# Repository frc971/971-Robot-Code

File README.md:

# **THIS REPO IS NOW ARCHIVED AND READ ONLY.**

# Introduction
This is FRC Team 971's main code repository. There are `README*` files throughout the source tree documenting specifics for their respective folders.

## Contributing
Submissions must be made under the terms of the following Developer Certificate of Origin.

By making a contribution to this project, I certify that:

        (a) The contribution was created in whole or in part by me and I
            have the right to submit it under the open source license
            indicated in the file; or

        (b) The contribution is based upon previous work that, to the best
            of my knowledge, is covered under an appropriate open source
            license and I have the right under that license to submit that
            work with modifications, whether created in whole or in part
            by me, under the same open source license (unless I am
            permitted to submit under a different license), as indicated
            in the file; or

        (c) The contribution was provided directly to me by some other
            person who certified (a), (b) or (c) and I have not modified
            it.

        (d) I understand and agree that this project and the contribution
            are public and that a record of the contribution (including all
            personal information I submit with it, including my sign-off) is
            maintained indefinitely and may be redistributed consistent with
            this project or the open source license(s) involved.

To do this, add the following to your commit message.  Gerrit will enforce that all commits have been signed off.

	Signed-off-by: Random J Developer <random@developer.example.org>

Git has support for adding Signed-off-by lines by using `git commit -s`, or you can setup a git commit hook to automatically sign off your commits.  [Stack Overflow](https://stackoverflow.com/questions/15015894/git-add-signed-off-by-line-using-format-signoff-not-working) has instructions for how to do this if you are interested.

## Table of contents
* [Pathway for new members](#pathway-for-new-members)
    * [Learning C++](#1-learning-c)
        * [XRP](#11-xrp)
    * [Gaining code access](#2-gaining-code-access)
    * [The codelab](#3-the-codelab)
* [Code Reviews](#code-reviews)
    * [Creating SSH Aliases](#creating-ssh-aliases)
* [Codelab](#codelab)
* [Other Information](#other-information)
    * [Roborio Kernel Traces](#roborio-kernel-traces)
    * [Notes on troubleshooting network setup](#notes-on-troubleshooting-network-setup)
    * [LSP Setup for Rust](#lsp-setup-for-rust)
    * [Other resources](#other-resources)

## Pathway for new members

### 1. Learning C++

C++ is what we use to program a majority of the code which runs on the robot.
We generally recommend [this course by codeacademy](https://www.codecademy.com/learn/learn-c-plus-plus) which goes over the basics of C++ as well as OOP.

#### 1.1 XRP

If you are unsure what to work on yet you can start on the [XRP Platform](https://docs.wpilib.org/en/stable/docs/xrp-robot/index.html).
Which basically lets you use smaller robots to learn about robotics through WPILib.

### 2. Gaining code access

You can follow [these steps](./documentation/tutorials/getting-started.md) to access the code.

There is also a document which goes over the basics of using both gerrit and git [here](./documentation/tutorials/git-and-gerrit-basics.md)

### 3. The codelab

Once you have an understanding of C++ and have gone through using all the steps needed to access the code you can start on the codelab, which is a directory living in `frc971/codelab/`. Which goes over a lot of the important introductory information that you need to know to get started when programming the robot.
You can read the [README](./frc971/codelab/README.md), which gives you introduces you to the codelab as well as the concepts you need to understand first.

## Code reviews
We want all code to at least have a second person look it over before it gets merged into the `main` branch. Gerrit has [extensive documentation on starting reviews](https://gerrit-review.googlesource.com/Documentation/user-upload.html).  There is also a good [intro User Guide](https://gerrit-review.googlesource.com/Documentation/intro-user.html) and an [intro to working with Gerrit](https://gerrit-review.googlesource.com/Documentation/intro-gerrit-walkthrough.html) and [Gerrit workflows](https://docs.google.com/presentation/d/1C73UgQdzZDw0gzpaEqIC6SPujZJhqamyqO1XOHjH-uk)

TL;DR: Make and commit your changes, do `git push origin HEAD:refs/for/main`, and then click on the provided link to add reviewers.  If you just upload a change without adding any reviewers, it might sit around for a long time before anybody else notices it.

[git-review](http://manpages.debian.org/cgi-bin/man.cgi?query=git-review) can make the upload process simpler.

To download a commit you can press d or click download on gerrit, then select fetch and paste the command in your terminal. Once you've done that you should switch to a new branch in order to make working on multiple commits easier.
You can do this by doing `git switch -c branch_name`, the branch name can be anything, and will only be public for you, so organize in whatever way you find easy to model.

When programming in C++ we follow [Google's C++ Style Guide](https://google.github.io/styleguide/cppguide.html)

Furthermore, you can run `bazel run //tools/lint:run-ci` to fix linter errors which appear on buildkite.

### Some other useful packages
These aren't strictly necessary to build the code, but Michael found the
additional tools provided by these packages useful to install when working with
the code on May 13, 2018.

> **Note**: These are for local install, most of these tools will be available on the build server

```bash
apt install git
apt install yapf3
apt install python3
apt install bazel
apt install clang-format
```

### Creating ssh aliases

It is also handy to alias logins to the raspberry pi's by adding lines like this to your ~/.ssh/config file:
```console
Host pi-7971-2
    User pi
    ForwardAgent yes
    HostName 10.79.71.102
    StrictHostKeyChecking no
```
or, for the roborio:
```
Host roborio-971
    User admin
    HostName 10.9.71.2
    StrictHostKeyChecking no
```
This allows you to use the alias to `ping`, `ssh`, or run commands like:
```
# Download code to robot #7971's raspberry pi #2
bazel run --config=armv7 -c opt //y2020:download_stripped -- pi-7971-2
```

## Other Information

### Roborio Kernel Traces

Currently (as of 2020.02.26), top tends to produce misleading statistics. As
such, you can get more useful information about CPU usage by using kernel
traces. Sample usage:
```console
# Note that you will need to install the trace-cmd package on the roborio.
# This may be not be a trivial task.
# Start the trace
trace-cmd start -e sched_switch -e workqueue
# Stop the trace
trace-cmd stop
# Save the trace to trace.dat
trace-cmd extract
```
You can then scp the `trace.dat` file to your computer and run `kernelshark
trace.dat` (may require installing the `kernelshark` apt package).

### LSP Setup for Rust

You can run `bazel run //tools:gen_rust_project` to generate a rust-project.json
file which rust-analyzer will pick up. You will need to execute this rule
periodically as it will be outdated whenever the BUILD files change.

> **Note** that there's currently no way to tell rust-analyzer *how* to compile
the code, so while it will give you completion support, go to definition, and
other niceties, it won't show compilation errors or warnings at this point.

### Other resources
  1. Intro to [AOS](./aos/README.md), our robot Operating System
  2. Introductory example: [ping/pong](./aos/events/README.md)
  3. Example of [logging](./aos/events/README.md)

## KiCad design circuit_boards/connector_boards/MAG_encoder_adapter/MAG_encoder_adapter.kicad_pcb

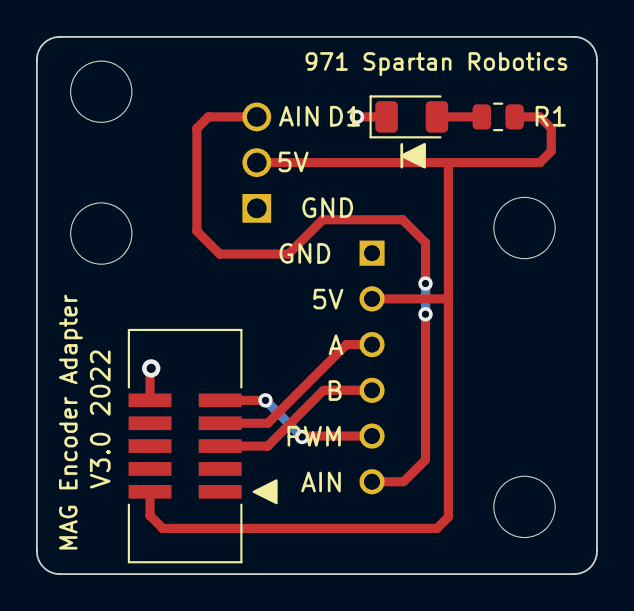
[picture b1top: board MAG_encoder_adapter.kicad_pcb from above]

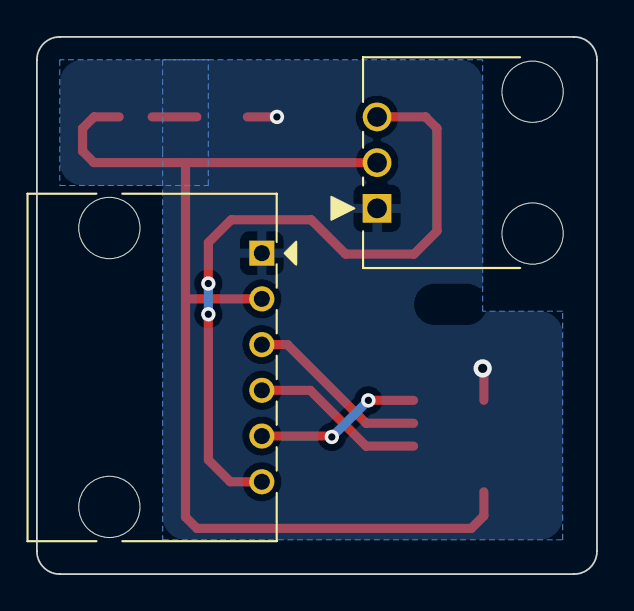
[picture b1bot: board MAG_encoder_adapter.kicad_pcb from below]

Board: 2 copper layers, 31.1 x 29.8 mm, 5 parts (2 on the bottom side), 7 nets.

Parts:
D1: LED; LED_1206_3216Metric
J2: POT; 70555-0002
J3: RIO; 705550005
R1: 2.0k 1%; R_0805_2012Metric
locked: Mag-encoder; 20021521-00010T1LF

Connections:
+5V: J2.2, J3.2, R1.2, locked.2
/A: J3.3, locked.7
/AIN: J2.3, J3.6
/B: J3.4, locked.5
/PWM: J3.5, locked.9
GND: D1.1 (K), J2.1, J3.1, locked.10
unnamed: D1.2 (A), R1.1

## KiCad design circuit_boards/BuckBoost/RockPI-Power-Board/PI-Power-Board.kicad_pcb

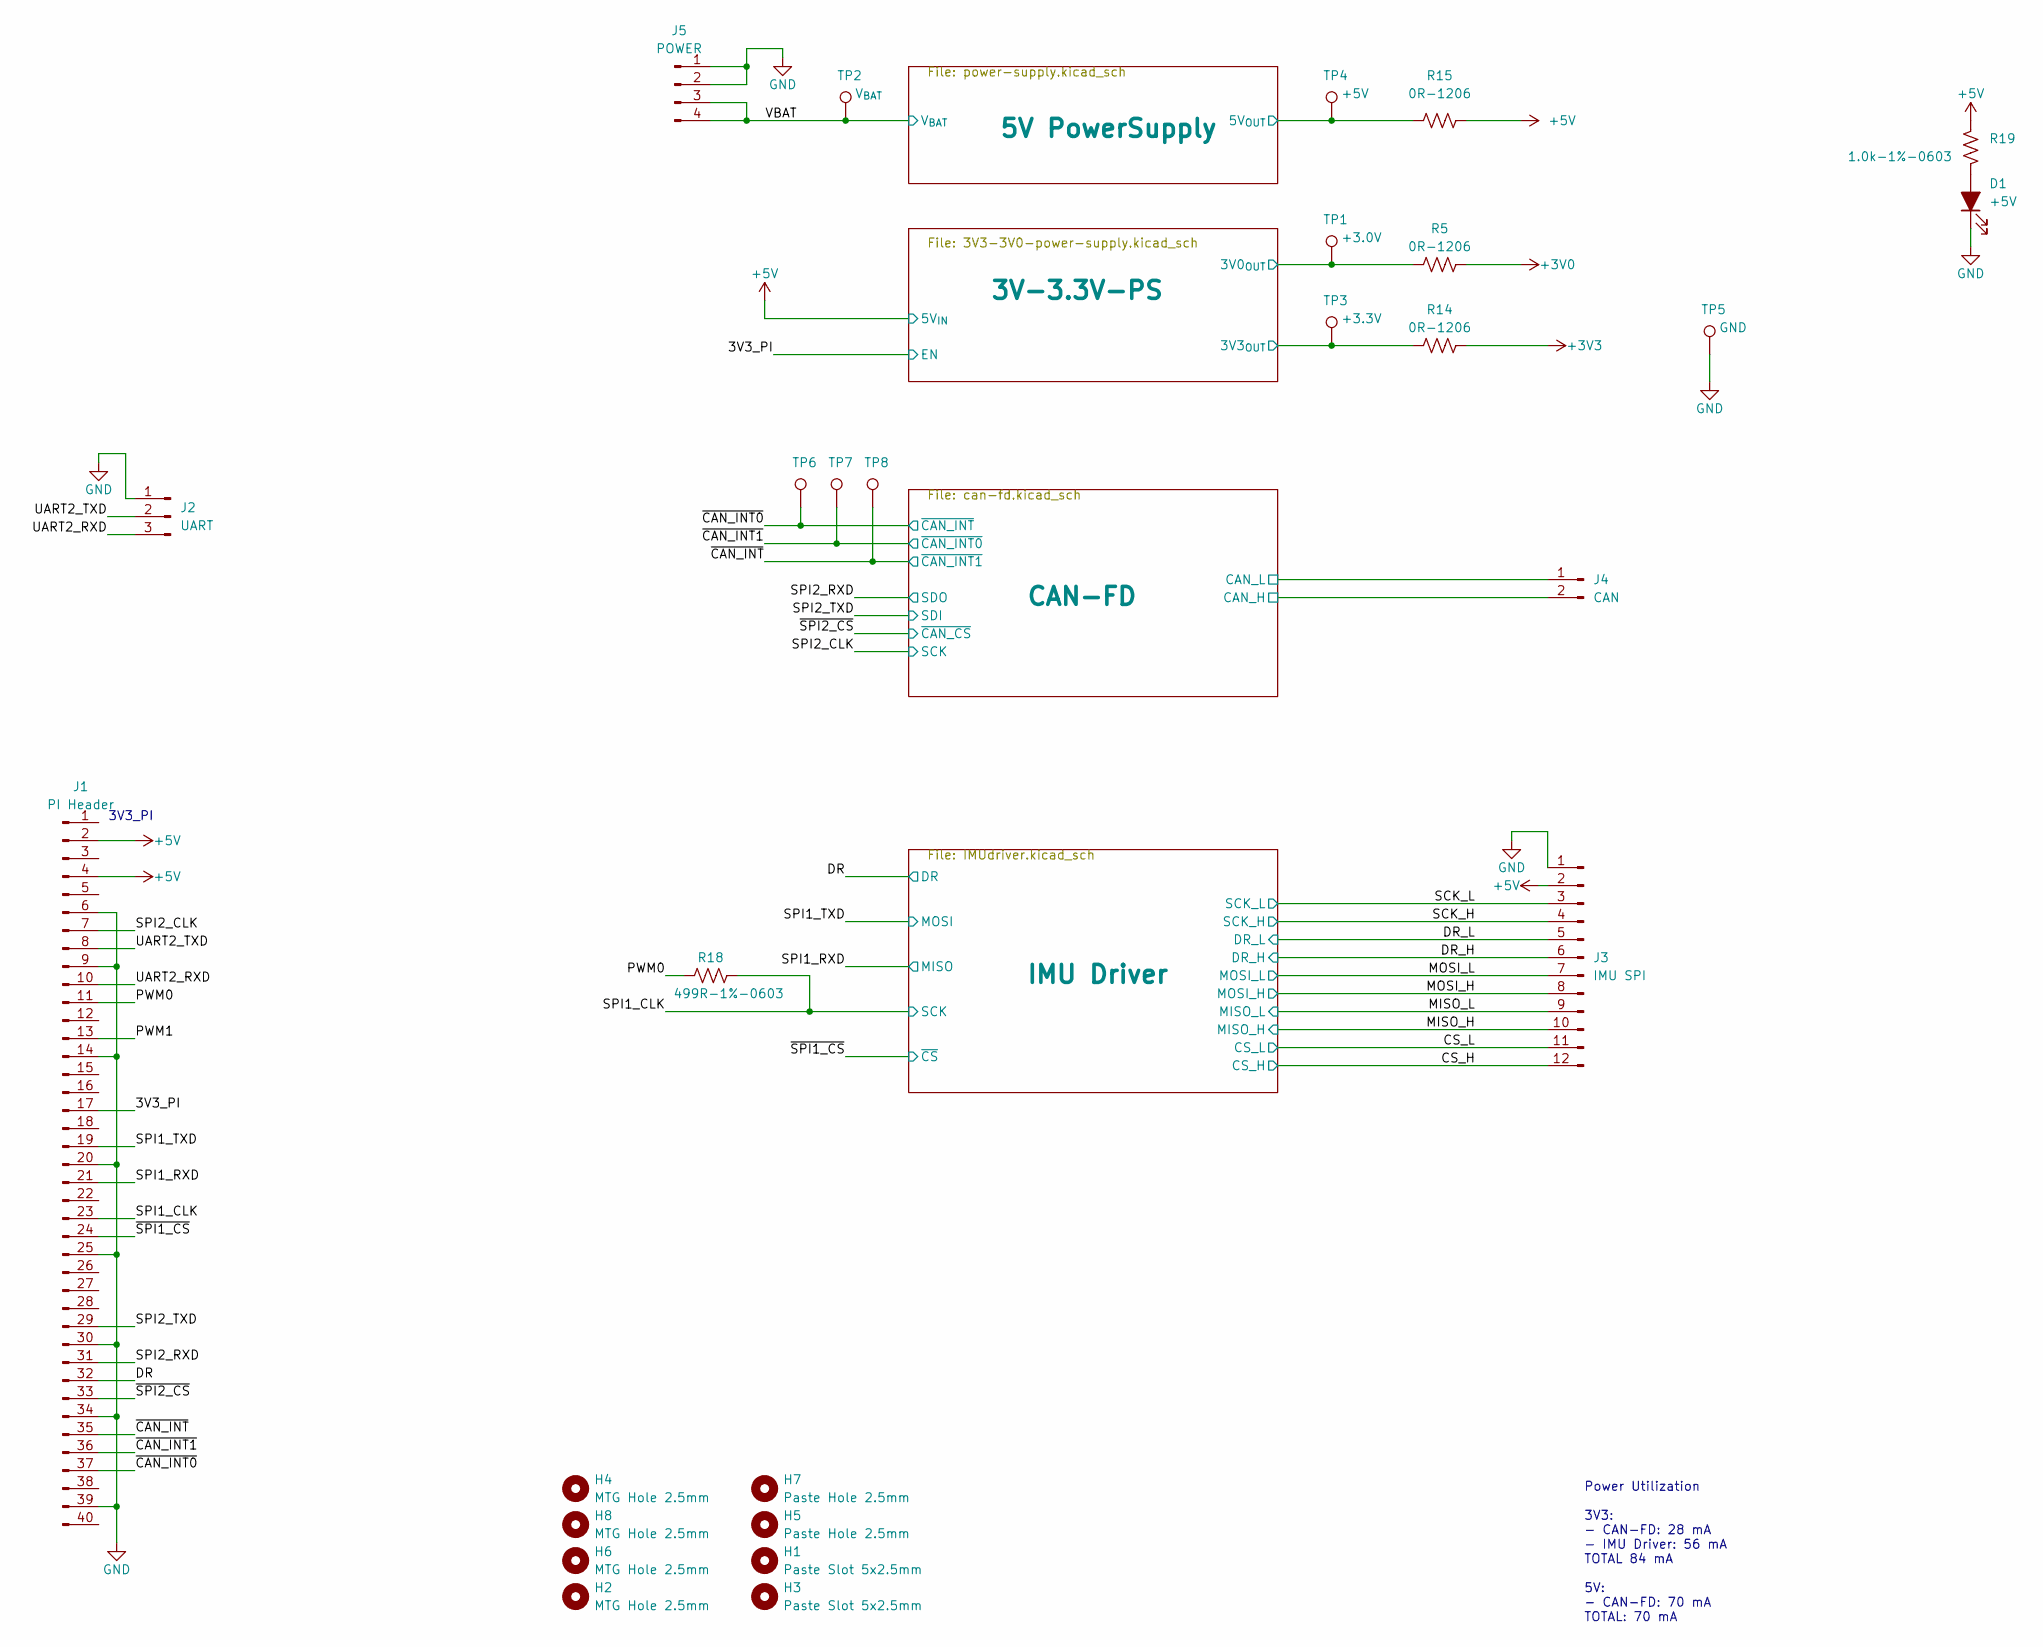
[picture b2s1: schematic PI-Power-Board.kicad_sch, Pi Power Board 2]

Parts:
D1: +5V; LED_1206_3216Metric; MFG P/N QTLP650D4TR
H1, H3: Paste Slot 5x2.5mm; PASTE-SLOT-5x2.5mm
H2, H4, H6, H8: MTG Hole 2.5mm; MountingHole_2.5mm
H5, H7: Paste Hole 2.5mm; PASTE-HOLE-2.5mm
J1: PI Header; M20-782045; MFG P/N M20-7812045
J2: UART; 70555-0002; MFG P/N 70555-0002
J3: IMU SPI; 70555-0011; MFG P/N 70555-0011
J4: CAN; 70555-0001; MFG P/N 70555-0001
J5: POWER; 70555-0003; MFG P/N 70555-0003
R5, R14, R15: 0R-1206; R_1206_3216Metric; MFG P/N RC1206JR-070RL
R18: 499R-1%-0603; R_0603_1608Metric; MFG P/N RC0603FR-07499RL
R19: 1.0k-1%-0603; R_0603_1608Metric; MFG P/N RC0603FR-071KL
TP1: +3.0V; TestPoint_Keystone_5000-5004_Miniature; MFG P/N 5002
TP2: V_{BAT}; TestPoint_Keystone_5000-5004_Miniature; MFG P/N 5002
TP3, TP6, TP7, TP8: +3.3V; TestPoint_Keystone_5000-5004_Miniature; MFG P/N 5002
TP4: +5V; TestPoint_Keystone_5000-5004_Miniature; MFG P/N 5002
TP5: GND; TestPoint_Keystone_5000-5004_Miniature; MFG P/N 5002

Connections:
+3V0: R5.2; also elsewhere on the board
+3V3: R14.2; also elsewhere on the board
+5V: J1.2, J1.4, J3.2, R15.2, R19.2; also elsewhere on the board
/3V3_PI: J1.17; also elsewhere on the board
/3V-3.3V-PS/3V0_{OUT}: R5.1, TP1.1; also elsewhere on the board
/3V-3.3V-PS/3V3_{OUT}: R14.1, TP3.1; also elsewhere on the board
/5V PowerSupply/V_{OSNS}: R15.1, TP4.1; also elsewhere on the board
/CAN-FD/CAN_H: J4.2; also elsewhere on the board
/CAN-FD/CAN_L: J4.1; also elsewhere on the board
/CS_H: J3.12; also elsewhere on the board
/CS_L: J3.11; also elsewhere on the board
/DR: J1.32; also elsewhere on the board
/DR_H: J3.6; also elsewhere on the board
/DR_L: J3.5; also elsewhere on the board
/MISO_H: J3.10; also elsewhere on the board
/MISO_L: J3.9; also elsewhere on the board
/MOSI_H: J3.8; also elsewhere on the board
/MOSI_L: J3.7; also elsewhere on the board
/PWM0: J1.11, R18.1
/PWM1: J1.13
/SCK_H: J3.4; also elsewhere on the board
/SCK_L: J3.3; also elsewhere on the board
/SPI1_CLK: J1.23, R18.2; also elsewhere on the board
/SPI1_RXD: J1.21; also elsewhere on the board
/SPI1_TXD: J1.19; also elsewhere on the board
/SPI2_CLK: J1.7; also elsewhere on the board
/SPI2_RXD: J1.31; also elsewhere on the board
/SPI2_TXD: J1.29; also elsewhere on the board
/UART2_RXD: J1.10, J2.3
/UART2_TXD: J1.8, J2.2
/VBAT: J5.3, J5.4, TP2.1; also elsewhere on the board
/~CAN_INT0: J1.37, TP6.1; also elsewhere on the board
/~CAN_INT1: J1.36, TP7.1; also elsewhere on the board
/~CAN_INT: J1.35, TP8.1; also elsewhere on the board
/~SPI1_CS: J1.24; also elsewhere on the board
/~SPI2_CS: J1.33; also elsewhere on the board
GND: D1.1 (K), J1.6, J1.9, J1.14, J1.20, J1.25, J1.30, J1.34, J1.39, J2.1, J3.1, J5.1, J5.2, TP5.1; also elsewhere on the board
unnamed: D1.2 (A), R19.1

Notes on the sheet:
3V3_PI
Power Utilization 3V3: - CAN-FD: 28 mA - IMU Driver: 56 mA TOTAL 84 mA 5V: - CAN-FD: 70 mA TOTAL: 70 mA

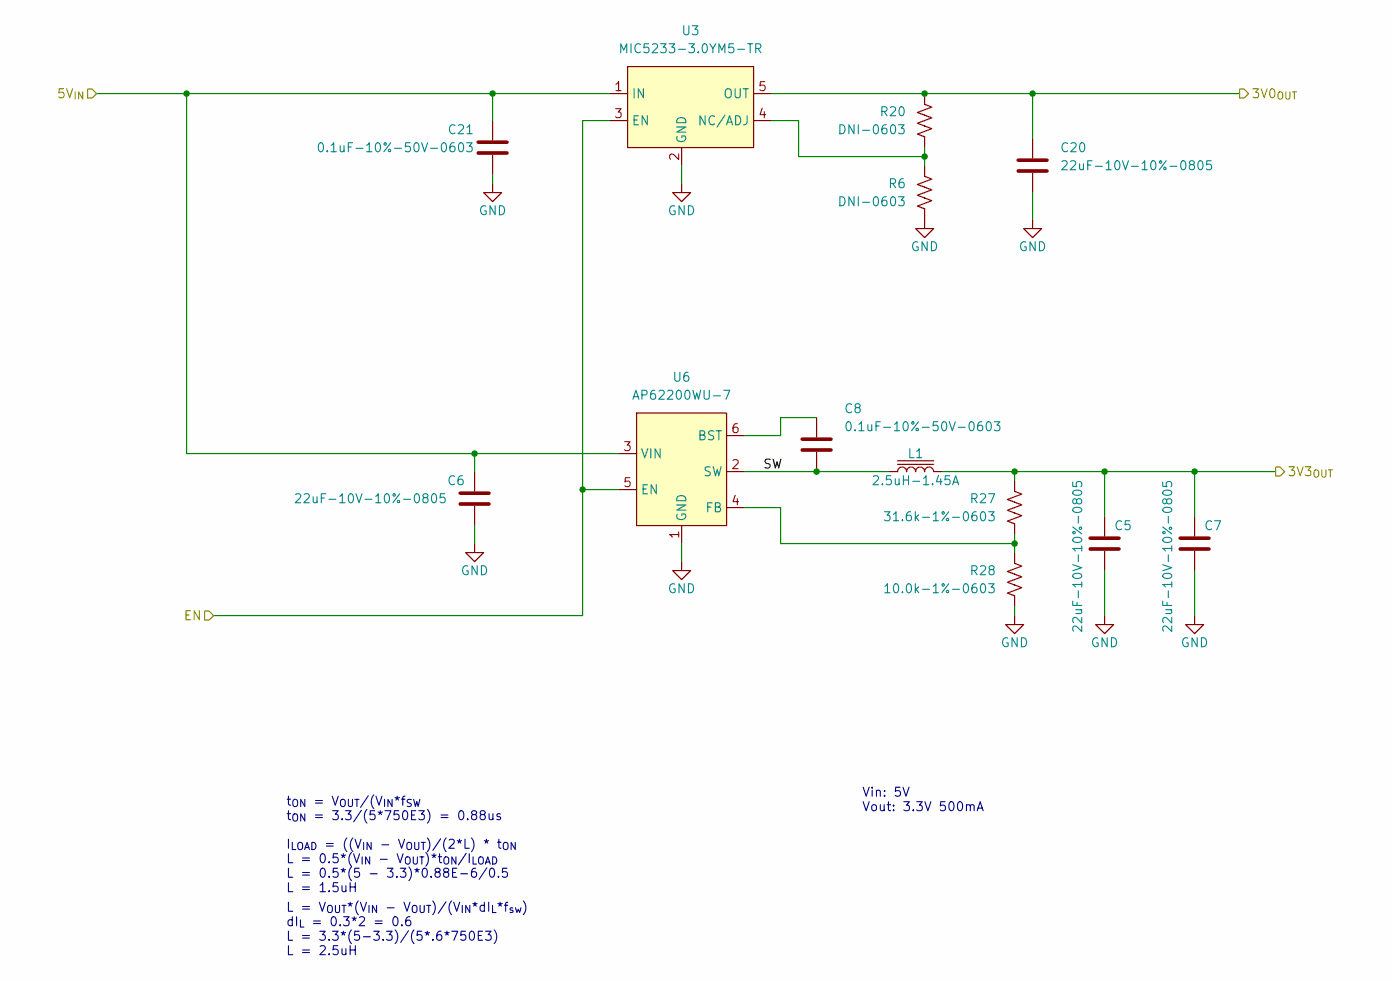
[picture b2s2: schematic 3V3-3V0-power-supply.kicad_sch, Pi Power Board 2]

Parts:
C5, C6, C7, C20: 22uF-10V-10%-0805; C_0805_2012Metric; MFG P/N CL21A226KPCLRNC
C8, C21: 0.1uF-10%-50V-0603; C_0603_1608Metric; MFG P/N CL10B104KB8NNNC
L1: 2.5uH-1.45A; WE-TPC-744031002; MFG P/N 744031002
R6, R20: DNI-0603; R_0603_1608Metric
R27: 31.6k-1%-0603; R_0603_1608Metric; MFG P/N RMCF0603FT31K6
R28: 10.0k-1%-0603; R_0603_1608Metric; MFG P/N RC0603FR-0710KL
U3: MIC5233-3.0YM5-TR; SOT-23-5; MFG P/N MIC5233-3.0YM5-TR
U6: AP62200WU-7; TSOT-23-6; MFG P/N AP62200WU-7

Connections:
+5V: C6.1, C21.1, U3.1 (IN), U6.3 (VIN); also elsewhere on the board
/3V3_PI: U3.3 (EN), U6.5 (EN); also elsewhere on the board
/3V-3.3V-PS/3V0_{OUT}: C20.1, R20.1, U3.5 (OUT); also elsewhere on the board
/3V-3.3V-PS/3V3_{OUT}: C5.1, C7.1, L1.2, R27.1; also elsewhere on the board
/3V-3.3V-PS/SW: C8.2, L1.1, U6.2 (SW)
GND: C5.2, C6.2, C7.2, C20.2, C21.2, R6.2, R28.2, U3.2 (GND), U6.1 (GND); also elsewhere on the board
unnamed: C8.1, U6.6 (BST)
unnamed: R6.1, R20.2, U3.4 (NC/ADJ)
unnamed: R27.2, R28.1, U6.4 (FB)

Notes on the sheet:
Vin: 5V Vout: 3.3V 500mA
I_{LOAD} = ((V_{IN} - V_{OUT})/(2*L) * t_{ON} L = 0.5*(V_{IN} - V_{OUT})*t_{ON}/I_{LOAD} L = 0.5*(5 - 3.3)*0.88E-6/0.5 L = 1.5uH
L = V_{OUT}*(V_{IN} - V_{OUT})/(V_{IN}*dI_{L}*f_{sw}) dI_{L} = 0.3*2 = 0.6 L = 3.3*(5-3.3)/(5*.6*750E3) L = 2.5uH
t_{ON} = V_{OUT}/(V_{IN}*f_{SW} t_{ON} = 3.3/(5*750E3) = 0.88us

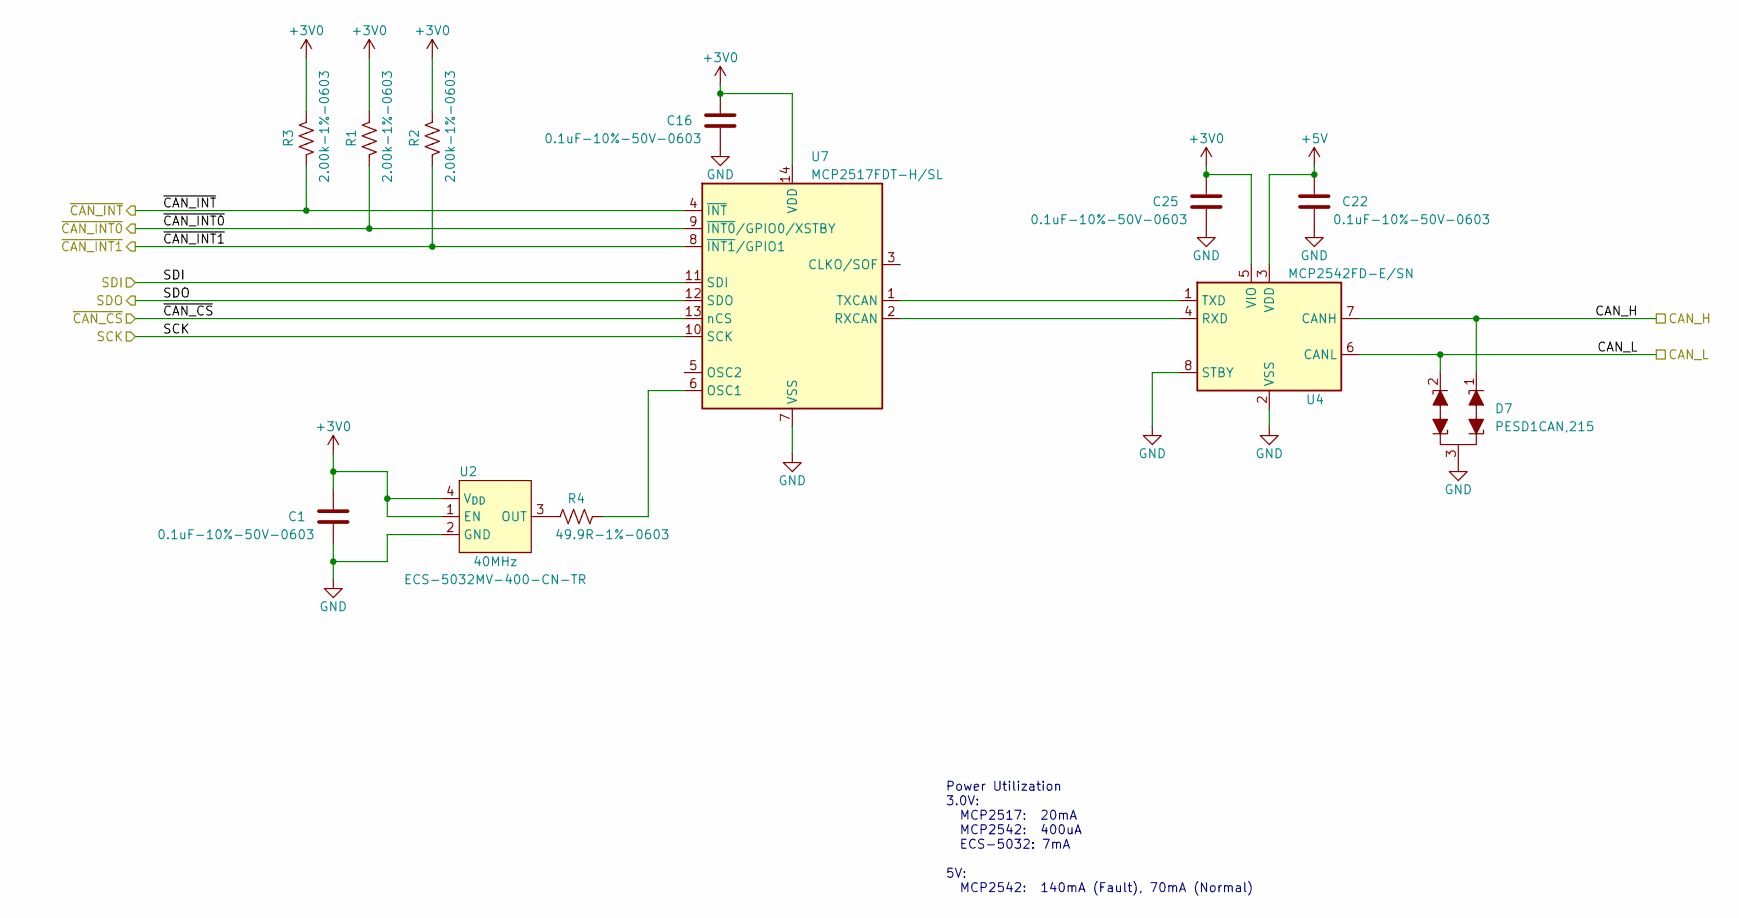
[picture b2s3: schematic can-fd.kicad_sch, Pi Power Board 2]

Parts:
C1, C16, C22, C25: 0.1uF-10%-50V-0603; C_0603_1608Metric; MFG P/N CL10B104KB8NNNC
D7: PESD1CAN; SOT-23; MFG P/N PESD1CAN,215
R1, R2, R3: 2.00k-1%-0603; R_0603_1608Metric; MFG P/N RC0603FR-072KL
R4: 49.9R-1%-0603; R_0603_1608Metric; MFG P/N RC0603FR-0749R9L
U2: 40MHz; ECS-5032MV; MFG P/N ECS-5032MV-400-CN-TR
U4: MCP2542FD-E/SN; SO-8_3.9x4.9mm_P1.27mm; MFG P/N MCP2542FD-E/SN
U7: MCP2517FDT-H/SL; SOIC-14_3.9x8.7mm_P1.27mm; MFG P/N MCP2517FDT-H/SL

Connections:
+3V0: C1.1, C16.1, C25.1, R1.1, R2.1, R3.1, U2.1 (EN), U2.4 (V_{DD}), U4.5 (VIO), U7.14 (VDD); also elsewhere on the board
+5V: C22.1, U4.3 (VDD); also elsewhere on the board
/CAN-FD/CAN_H: D7.1 (K1), U4.7 (CANH); also elsewhere on the board
/CAN-FD/CAN_L: D7.2 (K1), U4.6 (CANL); also elsewhere on the board
/SPI2_CLK: U7.10 (SCK); also elsewhere on the board
/SPI2_RXD: U7.12 (SDO); also elsewhere on the board
/SPI2_TXD: U7.11 (SDI); also elsewhere on the board
/~CAN_INT0: R3.2, U7.4 (~INT); also elsewhere on the board
/~CAN_INT1: R1.2, U7.9 (~INT0/GPIO0/XSTBY); also elsewhere on the board
/~CAN_INT: R2.2, U7.8 (~INT1/GPIO1); also elsewhere on the board
/~SPI2_CS: U7.13 (nCS); also elsewhere on the board
GND: C1.2, C16.2, C22.2, C25.2, D7.3 (KK), U2.2 (GND), U4.2 (VSS), U4.8 (STBY), U7.7 (VSS); also elsewhere on the board
unnamed: R4.1, U2.3 (OUT)
unnamed: R4.2, U7.6 (OSC1)
unnamed: U4.1 (TXD), U7.1 (TXCAN)
unnamed: U4.4 (RXD), U7.2 (RXCAN)

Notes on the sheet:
Power Utilization 3.0V: MCP2517: 20mA MCP2542: 400uA ECS-5032: 7mA 5V: MCP2542: 140mA (Fault), 70mA (Normal)

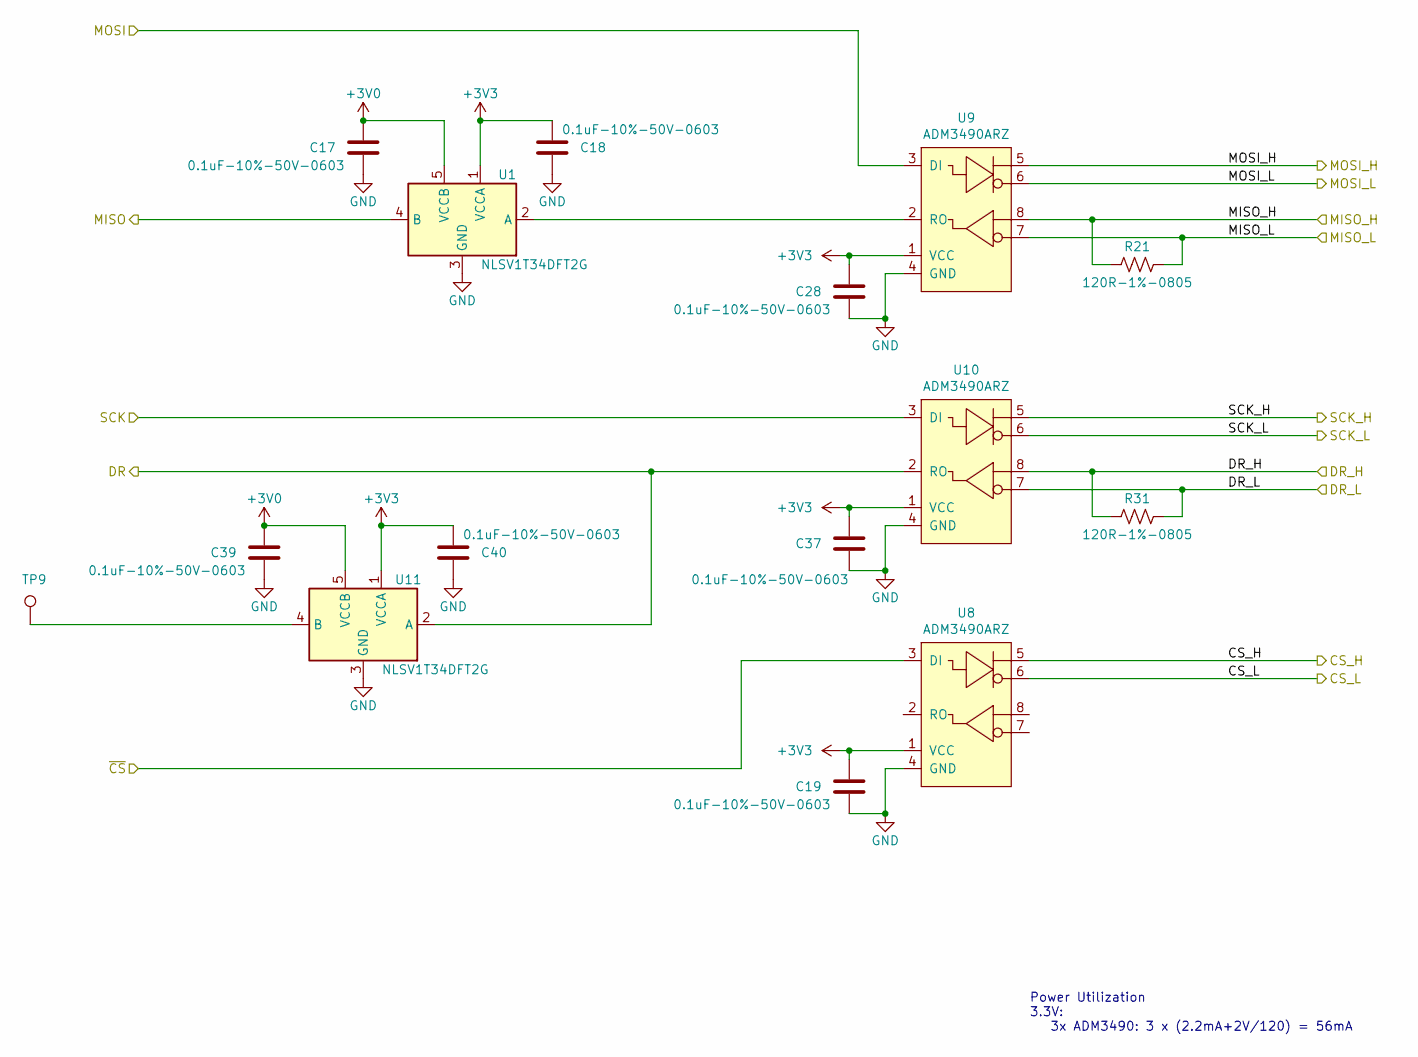
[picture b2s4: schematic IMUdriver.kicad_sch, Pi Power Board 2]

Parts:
C17, C18, C19, C28, C37, C39, C40: 0.1uF-10%-50V-0603; C_0603_1608Metric; MFG P/N CL10B104KB8NNNC
R21, R31: 120R-1%-0805; R_0805_2012Metric; MFG P/N RMCF0805FT120R
TP9: +3.3V; TestPoint_Keystone_5000-5004_Miniature; MFG P/N 5002
U1, U11: NLSV1T34DFT2G; SOT-353_SC-70-5; MFG P/N NLSV1T34DFT2G
U8, U9, U10: ADM3490ARZ; SO-8_3.9x4.9mm_P1.27mm; MFG P/N ADM3490ARZ

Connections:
+3V0: C17.1, C39.1, U1.5 (VCCB), U11.5 (VCCB); also elsewhere on the board
+3V3: C18.1, C19.1, C28.1, C37.1, C40.1, U1.1 (VCCA), U8.1 (VCC), U9.1 (VCC), U10.1 (VCC), U11.1 (VCCA); also elsewhere on the board
/CS_H: U8.5; also elsewhere on the board
/CS_L: U8.6; also elsewhere on the board
/DR: U10.2 (RO), U11.2 (A); also elsewhere on the board
/DR_H: R31.1, U10.8; also elsewhere on the board
/DR_L: R31.2, U10.7; also elsewhere on the board
/MISO_H: R21.1, U9.8; also elsewhere on the board
/MISO_L: R21.2, U9.7; also elsewhere on the board
/MOSI_H: U9.5; also elsewhere on the board
/MOSI_L: U9.6; also elsewhere on the board
/SCK_H: U10.5; also elsewhere on the board
/SCK_L: U10.6; also elsewhere on the board
/SPI1_CLK: U10.3 (DI); also elsewhere on the board
/SPI1_RXD: U1.4 (B); also elsewhere on the board
/SPI1_TXD: U9.3 (DI); also elsewhere on the board
/~SPI1_CS: U8.3 (DI); also elsewhere on the board
GND: C17.2, C18.2, C19.2, C28.2, C37.2, C39.2, C40.2, U1.3 (GND), U8.4 (GND), U9.4 (GND), U10.4 (GND), U11.3 (GND); also elsewhere on the board
unnamed: TP9.1, U11.4 (B)
unnamed: U1.2 (A), U9.2 (RO)

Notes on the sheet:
Power Utilization 3.3V: 3x ADM3490: 3 x (2.2mA+2V/120) = 56mA

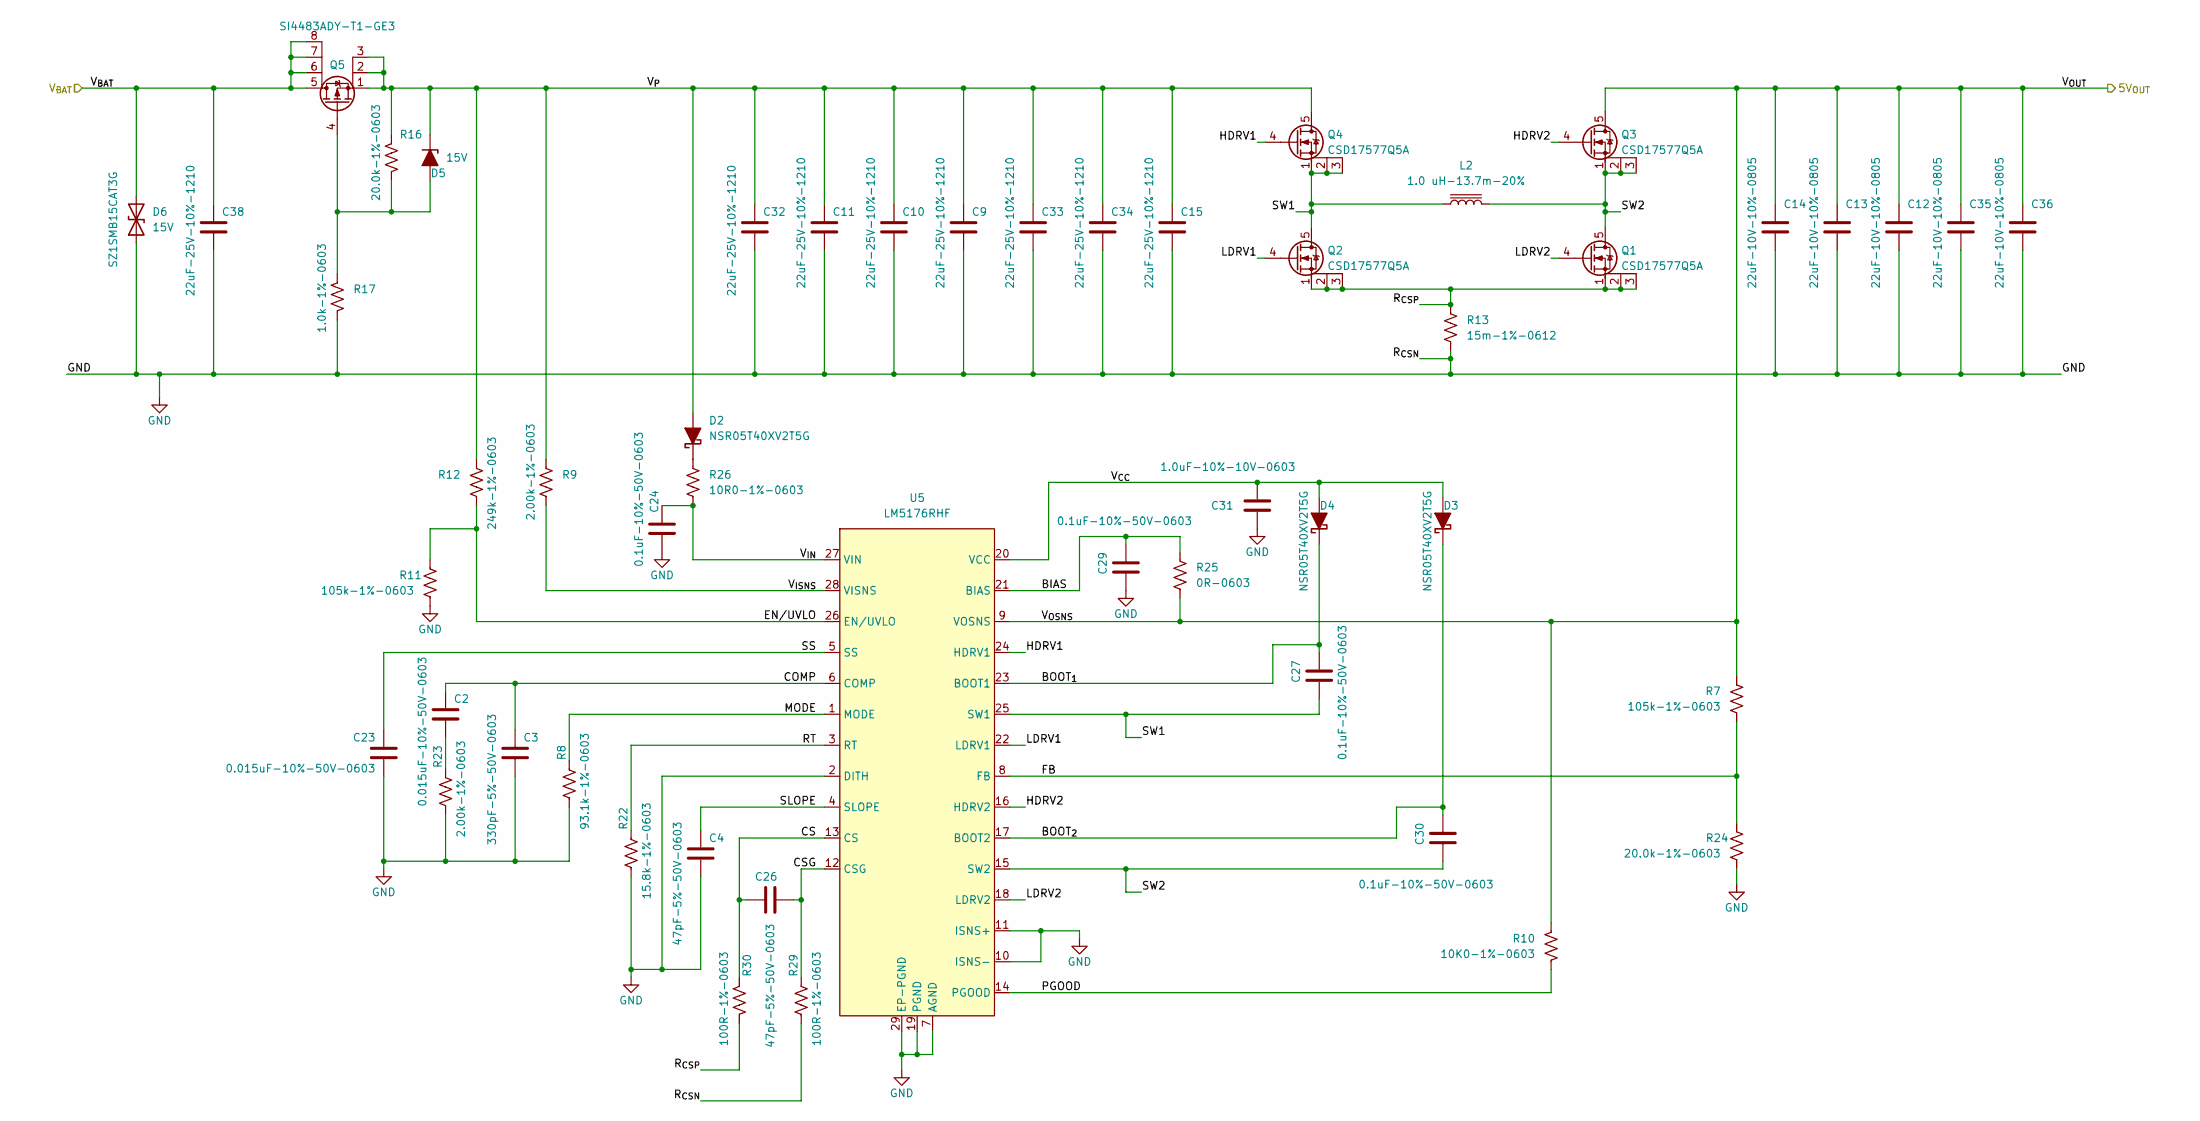
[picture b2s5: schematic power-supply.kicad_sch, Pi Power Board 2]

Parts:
C2, C23: 0.015uF-10%-50V-0603; C_0603_1608Metric; MFG P/N CC0603KRX7R9BB153
C3: 330pF-5%-50V-0603; C_0603_1608Metric; MFG P/N GCM1885C2A331FA16D
C4, C26: 47pF-5%-50V-0603; C_0603_1608Metric; MFG P/N CL10C470JB8NNNC
C9, C10, C11, C15, C32, C33, C34, C38: 22uF-25V-10%-1210; C_1210_3225Metric; MFG P/N GRM32ER61E226KE15L
C12, C13, C14, C35, C36: 22uF-10V-10%-0805; C_0805_2012Metric; MFG P/N CL21A226KPCLRNC
C24, C27, C29, C30: 0.1uF-10%-50V-0603; C_0603_1608Metric; MFG P/N CL10B104KB8NNNC
C31: 1.0uF-10%-10V-0603; C_0603_1608Metric; MFG P/N CL10B105KP8NNNC
D2, D3, D4: NSR05T40XV2T5G; D_SOD-523; MFG P/N NSR05T40XV2T5G
D5: 15V; D_SOD-123F; MFG P/N BZT52H-C15,115
D6: 15V; D_SMB; MFG P/N SZ1SMB15CAT3G
L2: 1.0 uH-13.7m-20%; IHLP2020CZER; MFG P/N IHLP2020CZER1R0M01
Q1, Q2, Q3, Q4: CSD17577Q5A; TI-SON5x6; MFG P/N CSD17577Q5A
Q5: SI4483ADY-T1-GE3; SOIC-8_3.9x4.9mm_P1.27mm; MFG P/N SI4483ADY-T1-GE3
R7, R11: 105k-1%-0603; R_0603_1608Metric; MFG P/N RC0603FR-07105KL
R8: 93.1k-1%-0603; R_0603_1608Metric; MFG P/N ERJ-3EKF9312V
R9, R23: 2.00k-1%-0603; R_0603_1608Metric; MFG P/N RC0603FR-072KL
R10: 10K0-1%-0603; R_0603_1608Metric; MFG P/N RC0603FR-0710KL
R12: 249k-1%-0603; R_0603_1608Metric; MFG P/N RC0603FR-07249KL
R13: 15m-1%-0612; R_0612_1632Metric; MFG P/N WU732BTTD15L0F
R16, R24: 20.0k-1%-0603; R_0603_1608Metric; MFG P/N RC0603FR-0720KL
R17: 1.0k-1%-0603; R_0603_1608Metric; MFG P/N RC0603FR-071KL
R22: 15.8k-1%-0603; R_0603_1608Metric; MFG P/N RC0603FR-0715K8L
R25: 0R-0603; R_0603_1608Metric; MFG P/N RMCF0603ZT0R00
R26: 10R0-1%-0603; R_0603_1608Metric; MFG P/N RC0603FR-0710RL
R29, R30: 100R-1%-0603; R_0603_1608Metric; MFG P/N RC0603FR-07100RL
U5: LM5176RHF; QFN-28-1EP_4x5mm_P0.5mm_EP2.55x3.55mm_ThermalVias; MFG P/N LM5176RHFT

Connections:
/5V PowerSupply/BIAS: C29.1, R25.1, U5.21 (BIAS)
/5V PowerSupply/BOOT_{1}: C27.1, D4.1 (K), U5.23 (BOOT1)
/5V PowerSupply/BOOT_{2}: C30.1, D3.1 (K), U5.17 (BOOT2)
/5V PowerSupply/COMP: C2.1, C3.1, U5.6 (COMP)
/5V PowerSupply/CS: C26.1, R30.1, U5.13 (CS)
/5V PowerSupply/CSG: C26.2, R29.1, U5.12 (CSG)
/5V PowerSupply/EN/UVLO: R11.1, R12.2, U5.26 (EN/UVLO)
/5V PowerSupply/FB: R7.2, R24.1, U5.8 (FB)
/5V PowerSupply/HDRV1: Q4.4 (G), U5.24 (HDRV1)
/5V PowerSupply/HDRV2: Q3.4 (G), U5.16 (HDRV2)
/5V PowerSupply/LDRV1: Q2.4 (G), U5.22 (LDRV1)
/5V PowerSupply/LDRV2: Q1.4 (G), U5.18 (LDRV2)
/5V PowerSupply/MODE: R8.1, U5.1 (MODE)
/5V PowerSupply/PGOOD: R10.2, U5.14 (PGOOD)
/5V PowerSupply/RT: R22.1, U5.3 (RT)
/5V PowerSupply/R_{CSP}: Q1.1 (S), Q1.2 (S), Q1.3 (S), Q2.1 (S), Q2.2 (S), Q2.3 (S), R13.1, R30.2
/5V PowerSupply/SLOPE: C4.1, U5.4 (SLOPE)
/5V PowerSupply/SS: C23.1, U5.5 (SS)
/5V PowerSupply/SW1: C27.2, L2.1, Q2.5 (D), Q4.1 (S), Q4.2 (S), Q4.3 (S), U5.25 (SW1)
/5V PowerSupply/SW2: C30.2, L2.2, Q1.5 (D), Q3.1 (S), Q3.2 (S), Q3.3 (S), U5.15 (SW2)
/5V PowerSupply/V_{CC}: C31.1, D3.2 (A), D4.2 (A), U5.20 (VCC)
/5V PowerSupply/V_{IN}: C24.1, R26.2, U5.27 (VIN)
/5V PowerSupply/V_{ISNS}: R9.2, U5.28 (VISNS)
/5V PowerSupply/V_{OSNS}: C12.1, C13.1, C14.1, C35.1, C36.1, Q3.5 (D), R7.1, R10.1, R25.2, U5.9 (VOSNS); also elsewhere on the board
/5V PowerSupply/V_{P}: C9.2, C10.2, C11.2, C15.2, C32.2, C33.2, C34.2, D2.2 (A), D5.1 (K), Q4.5 (D), Q5.1 (S), Q5.2 (S), Q5.3 (S), R9.1, R12.1, R16.2
/VBAT: C38.2, D6.2 (A2), Q5.5 (D), Q5.6 (D), Q5.7 (D), Q5.8 (D); also elsewhere on the board
GND: C3.2, C4.2, C9.1, C10.1, C11.1, C12.2, C13.2, C14.2, C15.1, C23.2, C24.2, C29.2, C31.2, C32.1, C33.1, C34.1, C35.2, C36.2, C38.1, D6.1 (A1), R8.2, R11.2, R13.2, R17.1, R22.2, R23.2, R24.2, R29.2, U5.2 (DITH), U5.7 (AGND), U5.10 (ISNS-), U5.11 (ISNS+), U5.19 (PGND), U5.29 (EP-PGND); also elsewhere on the board
unnamed: C2.2, R23.1
unnamed: D2.1 (K), R26.1
unnamed: D5.2 (A), Q5.4 (G), R16.1, R17.2

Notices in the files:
parts and their libraries:
Copyright 2021 Accelerated Designs. All rights reserved.
